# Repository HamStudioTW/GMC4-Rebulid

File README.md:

```                                                                     
  ╭──╮                        ╭──────────────────╮                  
  |  |                        |  ╭────────────╮  |        ╭──────────╮          
  |  │            ╭──╮        |  |            |  |        |  ╭────╮  ╰───────╮  
  |  ╰────────────╯  |        |  ╰────────────╯  |        |  |    |  ╭────╮  |  
  |  ╭────────────╮  |        |  ╭────────────╮  |        |  |    |  |    |  |  
  |  │            │  |        |  │            │  |        |  |    |  |    |  |  
  |  │            │  |        |  │            │  |        |  |    |  |    |  | 
  ╰──╯            ╰──╯        ╰──╯            ╰──╯        ╰──╯    ╰──╯    ╰──╯  Studio
```

# GMC4-Rebulid

This is Rebulid of "大人の科学マガジン(No.24): 4ビットマイコン" GMC4

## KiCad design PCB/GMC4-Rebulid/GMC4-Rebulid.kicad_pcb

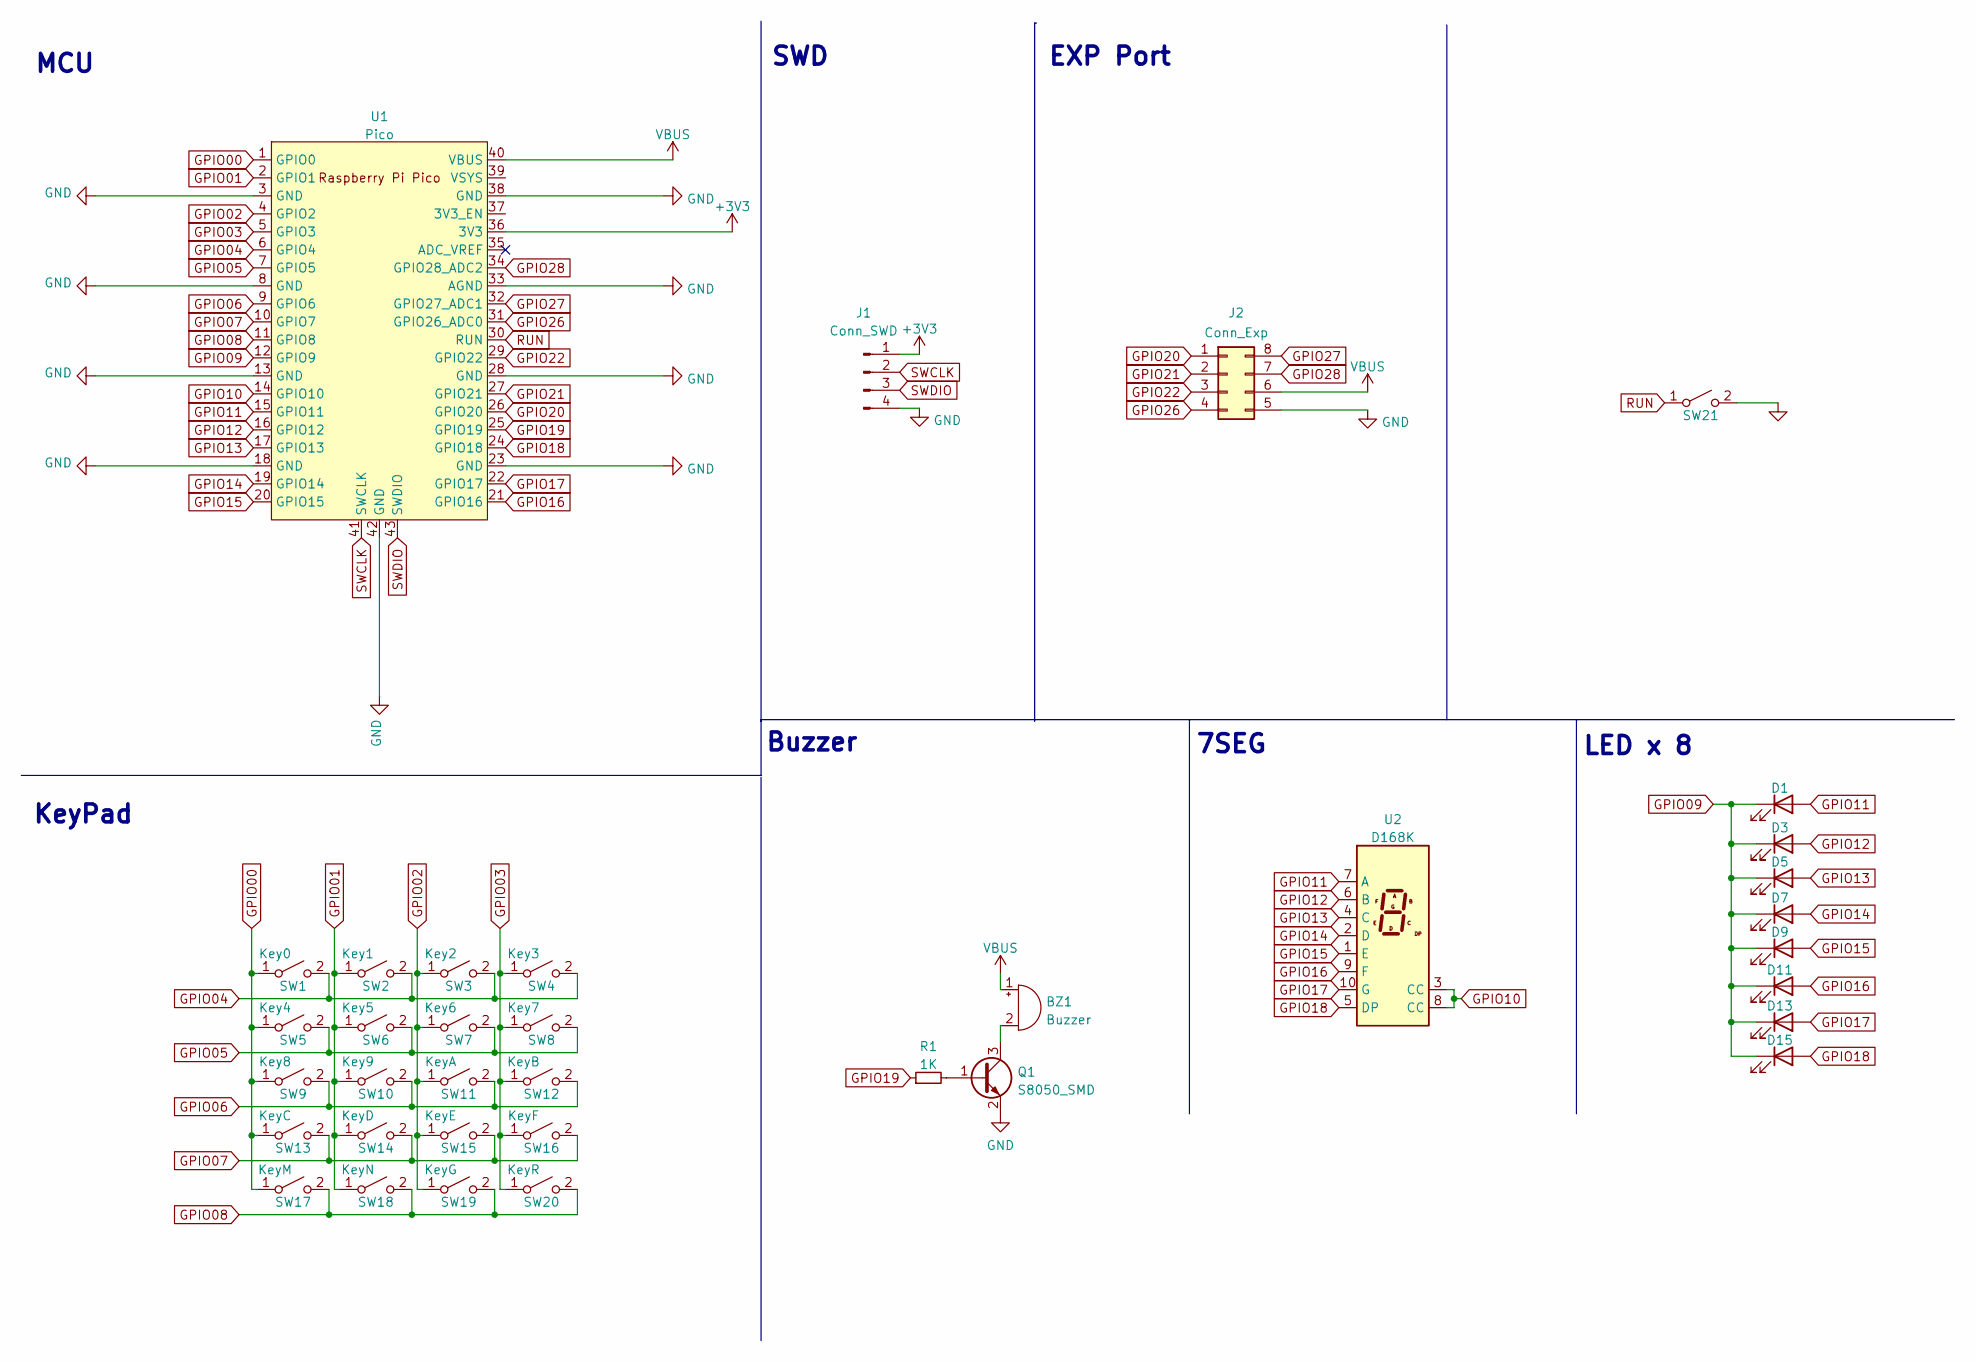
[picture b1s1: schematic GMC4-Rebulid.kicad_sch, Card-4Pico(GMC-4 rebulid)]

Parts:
BZ1: Buzzer; MagneticBuzzer_CUI_CMT-8504-100-SMT
D1, D3, D5, D7, D9, D11, D13, D15: LED; LED_0805_2012Metric_Pad1.15x1.40mm_HandSolder
J1: Conn_SWD; PinHeader_1x04_P2.54mm_Vertical
J2: Conn_Exp; PinHeader_2x04_P2.54mm_Vertical
Q1: S8050_SMD; SOT-23_Handsoldering
R1: 1K; R_0805_2012Metric_Pad1.20x1.40mm_HandSolder
SW1: Key0; SW_Push_1P1T_NO_6x6mm_H9.5mm
SW2: Key1; SW_Push_1P1T_NO_6x6mm_H9.5mm
SW3: Key2; SW_Push_1P1T_NO_6x6mm_H9.5mm
SW4: Key3; SW_Push_1P1T_NO_6x6mm_H9.5mm
SW5: Key4; SW_Push_1P1T_NO_6x6mm_H9.5mm
SW6: Key5; SW_Push_1P1T_NO_6x6mm_H9.5mm
SW7: Key6; SW_Push_1P1T_NO_6x6mm_H9.5mm
SW8: Key7; SW_Push_1P1T_NO_6x6mm_H9.5mm
SW9: Key8; SW_Push_1P1T_NO_6x6mm_H9.5mm
SW10: Key9; SW_Push_1P1T_NO_6x6mm_H9.5mm
SW11: KeyA; SW_Push_1P1T_NO_6x6mm_H9.5mm
SW12: KeyB; SW_Push_1P1T_NO_6x6mm_H9.5mm
SW13: KeyC; SW_Push_1P1T_NO_6x6mm_H9.5mm
SW14: KeyD; SW_Push_1P1T_NO_6x6mm_H9.5mm
SW15: KeyE; SW_Push_1P1T_NO_6x6mm_H9.5mm
SW16: KeyF; SW_Push_1P1T_NO_6x6mm_H9.5mm
SW17: KeyM; SW_Push_1P1T_NO_6x6mm_H9.5mm
SW18: KeyN; SW_Push_1P1T_NO_6x6mm_H9.5mm
SW19: KeyG; SW_Push_1P1T_NO_6x6mm_H9.5mm
SW20: KeyR; SW_Push_1P1T_NO_6x6mm_H9.5mm
SW21: SW_Push_1P1T_NO_6x6mm_H9.5mm
U1: Pico; RPi_Pico_SMD_TH
U2: D168K; 7SegmentLED_LTS6760_LTS6780

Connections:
+3V3: J1.1, U1.36 (3V3)
GND: J1.4, J2.5, Q1.2 (E), U1.3 (GND), U1.8 (GND), U1.13 (GND), U1.18 (GND), U1.23 (GND), U1.28 (GND), U1.33 (AGND), U1.38 (GND), U1.42 (GND); also elsewhere on the board
GPIO00: SW1.1 (A), SW5.1 (A), SW9.1 (A), SW13.1 (A), SW17.1 (A), U1.1 (GPIO0)
GPIO01: SW2.1 (A), SW6.1 (A), SW10.1 (A), SW14.1 (A), SW18.1 (A), U1.2 (GPIO1)
GPIO02: SW3.1 (A), SW7.1 (A), SW11.1 (A), SW15.1 (A), SW19.1 (A), U1.4 (GPIO2)
GPIO03: SW4.1 (A), SW8.1 (A), SW12.1 (A), SW16.1 (A), SW20.1 (A), U1.5 (GPIO3)
GPIO04: SW1.2 (B), SW2.2 (B), SW3.2 (B), SW4.2 (B), U1.6 (GPIO4)
GPIO05: SW5.2 (B), SW6.2 (B), SW7.2 (B), SW8.2 (B), U1.7 (GPIO5)
GPIO06: SW9.2 (B), SW10.2 (B), SW11.2 (B), SW12.2 (B), U1.9 (GPIO6)
GPIO07: SW13.2 (B), SW14.2 (B), SW15.2 (B), SW16.2 (B), U1.10 (GPIO7)
GPIO08: SW17.2 (B), SW18.2 (B), SW19.2 (B), SW20.2 (B), U1.11 (GPIO8)
GPIO09: D1.1 (K), D3.1 (K), D5.1 (K), D7.1 (K), D9.1 (K), D11.1 (K), D13.1 (K), D15.1 (K), U1.12 (GPIO9)
GPIO10: U1.14 (GPIO10), U2.3 (CC), U2.8 (CC)
GPIO11: D1.2 (A), U1.15 (GPIO11), U2.7 (A)
GPIO12: D3.2 (A), U1.16 (GPIO12), U2.6 (B)
GPIO13: D5.2 (A), U1.17 (GPIO13), U2.4 (C)
GPIO14: D7.2 (A), U1.19 (GPIO14), U2.2 (D)
GPIO15: D9.2 (A), U1.20 (GPIO15), U2.1 (E)
GPIO16: D11.2 (A), U1.21 (GPIO16), U2.9 (F)
GPIO17: D13.2 (A), U1.22 (GPIO17), U2.10 (G)
GPIO18: D15.2 (A), U1.24 (GPIO18), U2.5 (DP)
GPIO19: R1.1, U1.25 (GPIO19)
GPIO20: J2.1, U1.26 (GPIO20)
GPIO21: J2.2, U1.27 (GPIO21)
GPIO22: J2.3, U1.29 (GPIO22)
GPIO26: J2.4, U1.31 (GPIO26_ADC0)
GPIO27: J2.8, U1.32 (GPIO27_ADC1)
GPIO28: J2.7, U1.34 (GPIO28_ADC2)
unnamed: BZ1.2 (+), Q1.3 (C)
unnamed: Q1.1 (B), R1.2
RUN: SW21.1 (A), U1.30 (RUN); also elsewhere on the board
SWCLK: J1.2, U1.41 (SWCLK)
SWDIO: J1.3, U1.43 (SWDIO)
VBUS: BZ1.1 (-), J2.6, U1.40 (VBUS)

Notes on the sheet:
KeyPad
Buzzer
SWD
MCU
EXP Port
LED x 8
7SEG

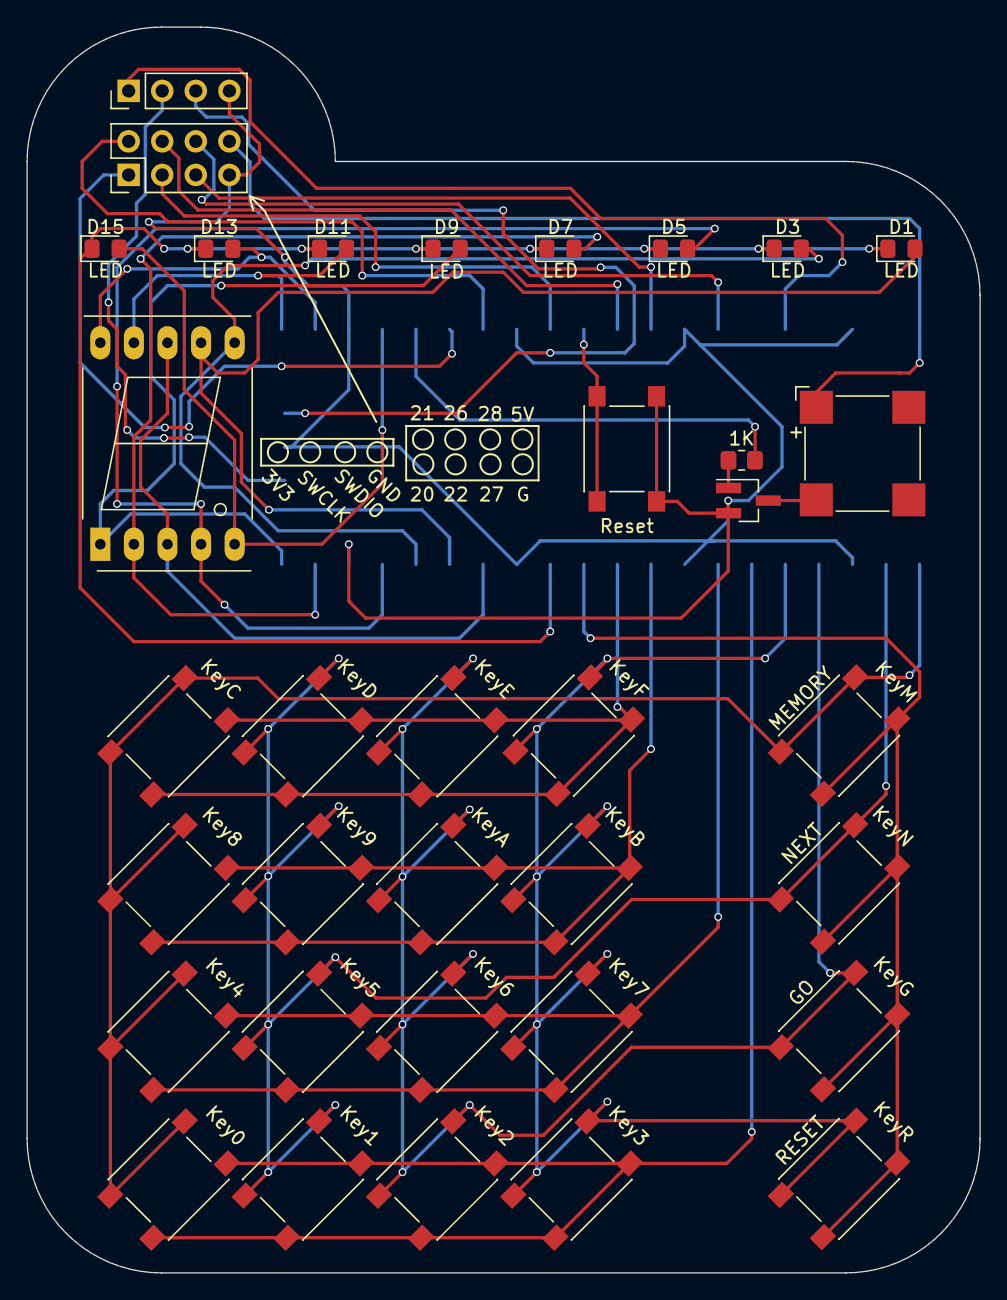
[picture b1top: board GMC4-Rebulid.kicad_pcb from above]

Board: 2 copper layers, 72.1 x 94.2 mm, 36 parts (1 on the bottom side), 34 nets.

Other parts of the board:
Reset: Hard Reset; SW_Push_1P1T_NO_6x6mm_H9.5mm

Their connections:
GND: Reset.2 (B); also elsewhere on the board
RUN: Reset.1 (A); also elsewhere on the board
